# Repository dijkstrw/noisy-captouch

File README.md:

Noisy captouch
==============

Toggling a lamp by touching its plastic base.

This project adds capacitive touch to an IKEA Jansjo light. An MSP430 on a
custom pcb is installed in between the lamp power supply and the lamp. The
MSP430 detects touches using a sensor pad in the base of the lamp, under the
ABS cover.

Touch algorithm
---------------
The measurement happens in a number of steps:
- first we build up a sliding sample window of 16 measurements
  (sum). This also provides us with a moving average (sum/16).

- we calculate a derivative = moving average - current measurement.

- if the derivative is positive: the measurement indicates that the
  counter wrapped less times than expected; which can be an indication
  of increased capacitance due to a touch event.

- if the derivative is higher than a preset threshold (minimum
  required change) we add part of it to the integral. Note that only
  part is considered, to make sure we need multiple "positive"
  measurements in sequence before we signal a touch event.

- if the integral has reached a preset threshold we signal a touch
  event, if not, we leak away some of our integrand to make sure the
  integral reports over a recent period only.

This algorithm tries to cater for a number of things:

- Atmospheric changes will change the measured capacitance, so we must
  take measurement drift into account.

- The electrodes are very sensitive and will pickup any large enough
  emf spikes, so we cannot trust single measured capacitance changes.

- If the emf spikes are high enough almost arbitrary measurements are
  possible, so we need to limit their contribution to integrand.

Complications
-------------

1. Power for the msp430 comes from a wallwart that also feeds the
   lamp. When the lamp is off, only the msp430 is drawing
   current. When the lamp is on an additional 500mA is drawn from the
   wallwart. This transition causes unwanted powersupply noise that
   interferes with the measurements.

2. When programming and debugging the ground is connected to the
   programmer ground. The effect of point 1 can then be
   underestimated. It is best to use an usb isolator when programming.

3. There are no right values for the capacitive touch thresholds, as
   these depend on the capacitive measurement, which in turn depend on
   your touch pad geometry. Especially for home built arbitrary sized
   pads as lamp bases, the values will differ between pads.

USCI
----
By using WDT for measurement we have enough of Timer0 left to do
bitbanging serial for non-USCI MSPs. (msp430g2452).

References
----------
- [Benn Thomsen, Capacitive Touch examples, March 2016](https://github.com/bennthomsen/CapacitiveTouch)
- Brandon Elliott/D. Dang, Texas Instruments Inc., November 2010

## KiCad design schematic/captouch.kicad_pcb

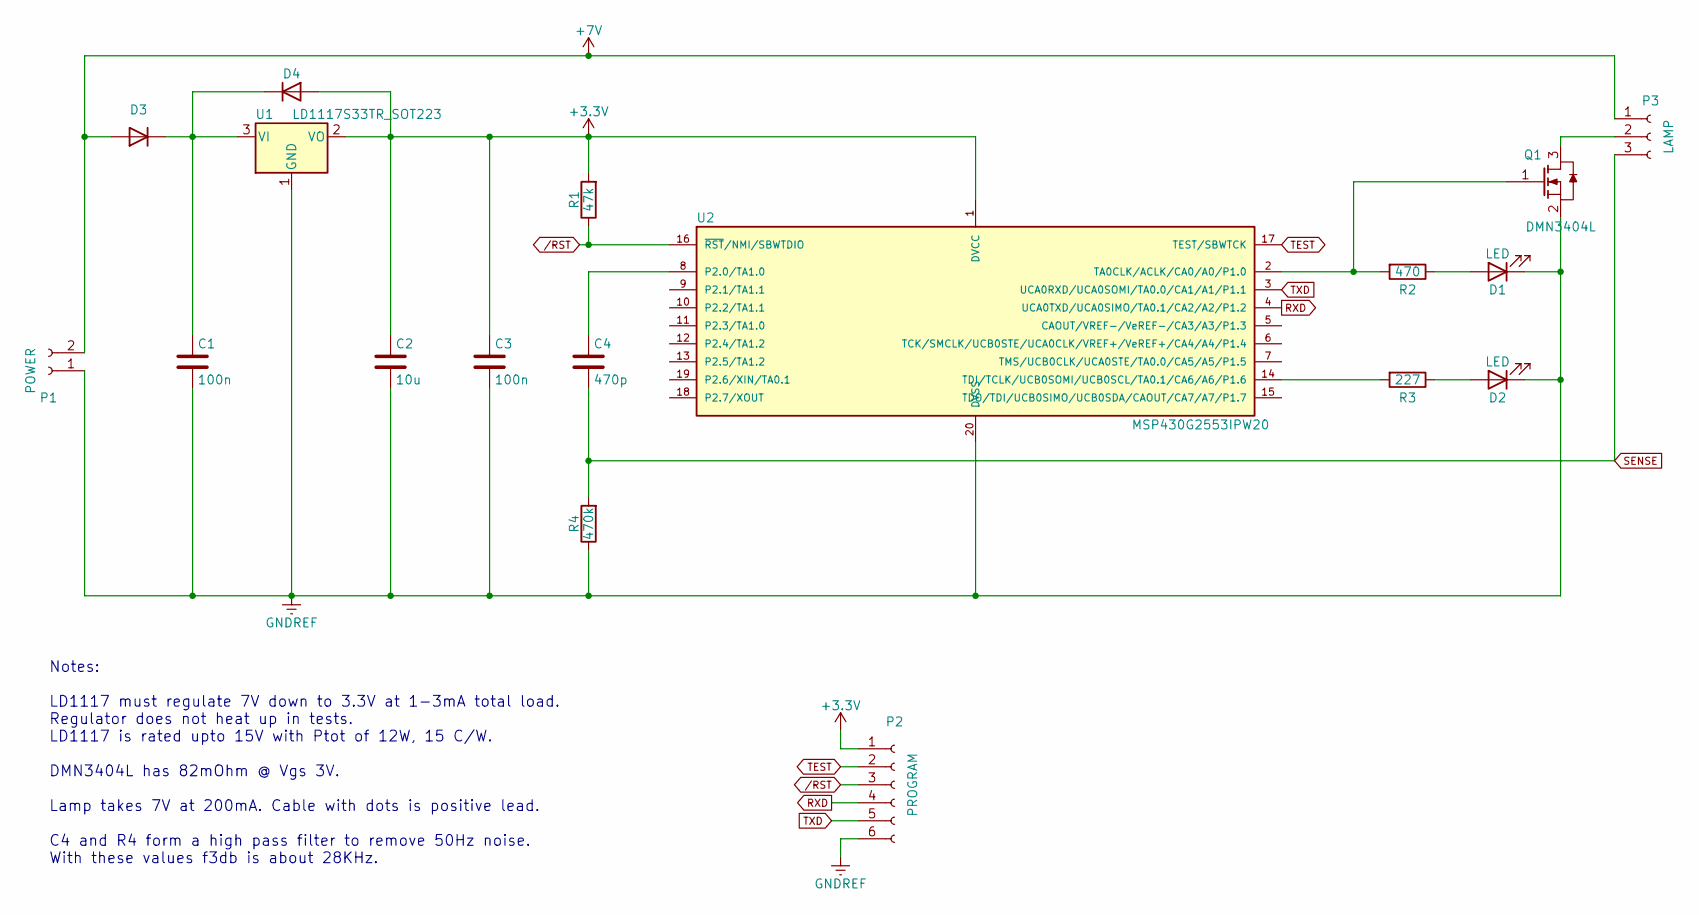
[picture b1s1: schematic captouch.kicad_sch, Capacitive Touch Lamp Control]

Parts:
C1, C3: 100n; C_0805
C2: 10u; C_1210
C4: 470p; C_0805
D1, D2: LED; LED_1206
D3, D4: D; SMD-1206_Pol
P1: POWER; P_1,5-2
P2: PROGRAM; Pin_Header_Angled_1x06
P3: LAMP; P_1,5-3
Q1: DMN3404L; SOT-23
R1: 47k; R_0805
R2: 470; R_0805
R3: 227; R_0805
R4: 470k; R_0805
U1: LD1117S33TR_SOT223; SOT-223-3_TabPin2
U2: MSP430G2553IPW20; TSSOP-20_4.4x6.5mm_Pitch0.65mm

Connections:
+3.3V: C2.1, C3.1, D4.2 (A), P2.1, R1.2, U1.2 (VO), U2.1 (DVCC)
+7V: D3.2 (A), P1.2, P3.1
GNDREF: C1.2, C2.2, C3.2, D1.1 (K), D2.1 (K), P1.1, P2.6, Q1.2 (S), R4.1, U1.1 (GND), U2.20 (DVSS)
unnamed: C1.1, D3.1 (K), D4.1 (K), U1.3 (VI)
unnamed: P3.2, Q1.3 (D)
unnamed: Q1.1 (G), R2.2, U2.2 (TA0CLK/ACLK/CA0/A0/P1.0)
unnamed: D1.2 (A), R2.1
unnamed: D2.2 (A), R3.1
unnamed: C4.1, U2.8 (P2.0/TA1.0)
unnamed: R3.2, U2.14 (TDI/TCLK/UCB0SOMI/UCB0SCL/TA0.1/CA6/A6/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)
RXD: P2.4, U2.4 (UCA0TXD/UCA0SIMO/TA0.1/CA2/A2/P1.2)
SENSE: C4.2, P3.3, R4.2
TEST: P2.2, U2.17 (TEST/SBWTCK)
TXD: P2.5, U2.3 (UCA0RXD/UCA0SOMI/TA0.0/CA1/A1/P1.1)
/RST: P2.3, R1.1, U2.16 (~RST/NMI/SBWTDIO)

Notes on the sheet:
Notes: LD1117 must regulate 7V down to 3.3V at 1-3mA total load. Regulator does not heat up in tests. LD1117 is rated upto 15V with Ptot of 12W, 15 C/W. DMN3404L has 82mOhm @ Vgs 3V. Lamp takes 7V at 200mA. Cable with dots is positive lead. C4 and R4 form a high pass filter to remove 50Hz noise. Wi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

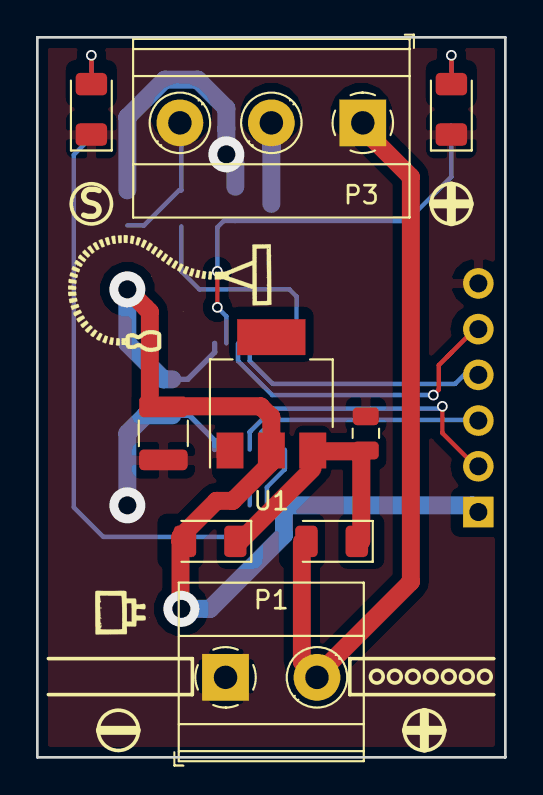
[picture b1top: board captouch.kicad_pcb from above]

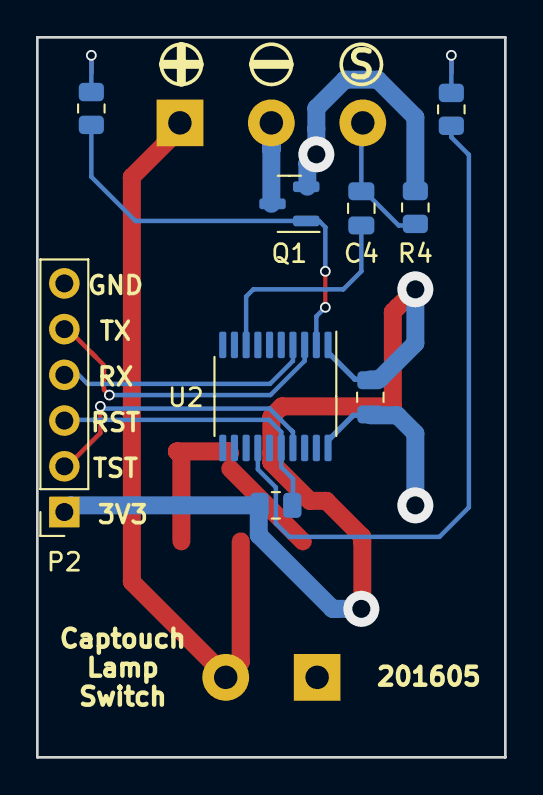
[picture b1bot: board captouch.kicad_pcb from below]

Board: 2 copper layers, 26.0 x 40.0 mm, 19 parts (9 on the bottom side), 15 nets.

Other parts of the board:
  : lamp

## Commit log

2018-08-04 root commit
2018-08-04 Code cleanup
2018-08-04 Further code cleanup
2018-08-04 Added documentation
2018-08-04 Added better heuristics at turnon
    Measurement is now faster at expense of more power. Green led turns on
    at powerup to show the user that we are calibrating. Measurement now
    runs longer to enable a better read + a higher level is now needed to
    turn on. Also turn on/off time is faster.
2018-08-04 Added a moving average to deal with small fluctuations
2018-08-04 Finished routing
    Artwork is next
2018-08-04 Added logos
2018-08-04 Started layout
2018-08-04 Cleaned up source
2018-08-04 Incorporated Martins schematic comments
2018-08-04 Source from github slightly modified for my sensor
2018-08-04 Added schematic, started pcb
2018-08-04 Rev 1, as fabbed by pcbway
2018-08-04 Added high pass filter
2018-08-04 Archived footprints, rev 2 schematic
    Fet footprint was wrong. Fixed in this schematic.
2018-08-04 Allow measurement window to drift + reset when keyed
    Measurement window can now drift slowly up and down, to account for
    environmental changes. A state machine that was present before but not
    explicit replaces the spaghetti ifs that came before. At key, the
    measurement window is reset to ensure that we know the current average
    measurement and are able to respond to change.
    We know that a person's touch would increase the capacitance, and thus
2018-08-04 Updated uart source for correct tx/rx mapping
2018-08-04 More little adjustments + logo
2018-08-04 Added auto timer off
2018-08-04 Added measurement notes
2018-08-04 Added measurement and high pass calc
2018-08-29 Added initial readme
2018-09-28 Add pictures
2023-04-01 Update readme
    - With latest render of v2 pcb
    - With more information about the algorithm
    - Remove old measurements information
2023-04-01 Sense algorithm now requires consecutive touching
    The sense algorithm now detects large changes in capacitance, and
    requires several large changes over time before it will signal a
    touch.
    There are a number of moving parts: a moving average, a derivative and
    and integral.
    - We take the average over the last 16 measurements, taking only those
2023-04-01 Adjusted for new msp430-gcc
2023-04-01 Adjusted thresholds using usb isolation
    Document the complications in README.
2023-04-01 Describe algorithm, make sure default values are sensible
2023-04-01 Update schematic to kicad 6
    I wanted renders of the schematics, so adjusted all components to
    kicad standard components. This way we also get to the associated 3d
    models.
2023-04-01 Adjust touch algorithm to take atmospheric drift into account
